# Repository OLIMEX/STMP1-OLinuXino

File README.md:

# STMP1-OLinuXino

STMP1 (es-ti-em-pai) OLinuXino (o-linux-ino) is based on STM32MP1XX Dual Core Cortex-A7 + Cortex-M4 microprocessors from ST Microelectronics. The Cortex-A7 can run Linux/Android OS while Cortex-M4 handle Real-Time events.

Features are:

- mainline Linux support
- automotive -40+125C operating temperature on all devices!
- 1GB DDR3L
- Gigabit Ethernet interface
- Three USB 2.0
- Two FD-CAN
- Two ADC
- Two DAC
- Camera IF
- Six I2C
- Three I2S
- Three SD MMC
- FMC (NAND) Flash
- Six SPI
- Four UART
- MIPI DSI 3Gb (157 only)
- Secure Boot
- Crypto Hash (C version only)

STMP1-OLinuXino is designed in the same size and connector locations as A20-OLinuXino-LIME2 so being replacable and pin to pin compatible. 

STMP1-OLinuXino is manufactured in -40+125C operating temperature and targets industrial applications.

# License
- Hardware is with CERN OHL v1.2 license
- Software is with GPLv3 license
- Documentation is with CC BY-SA 4.0 license

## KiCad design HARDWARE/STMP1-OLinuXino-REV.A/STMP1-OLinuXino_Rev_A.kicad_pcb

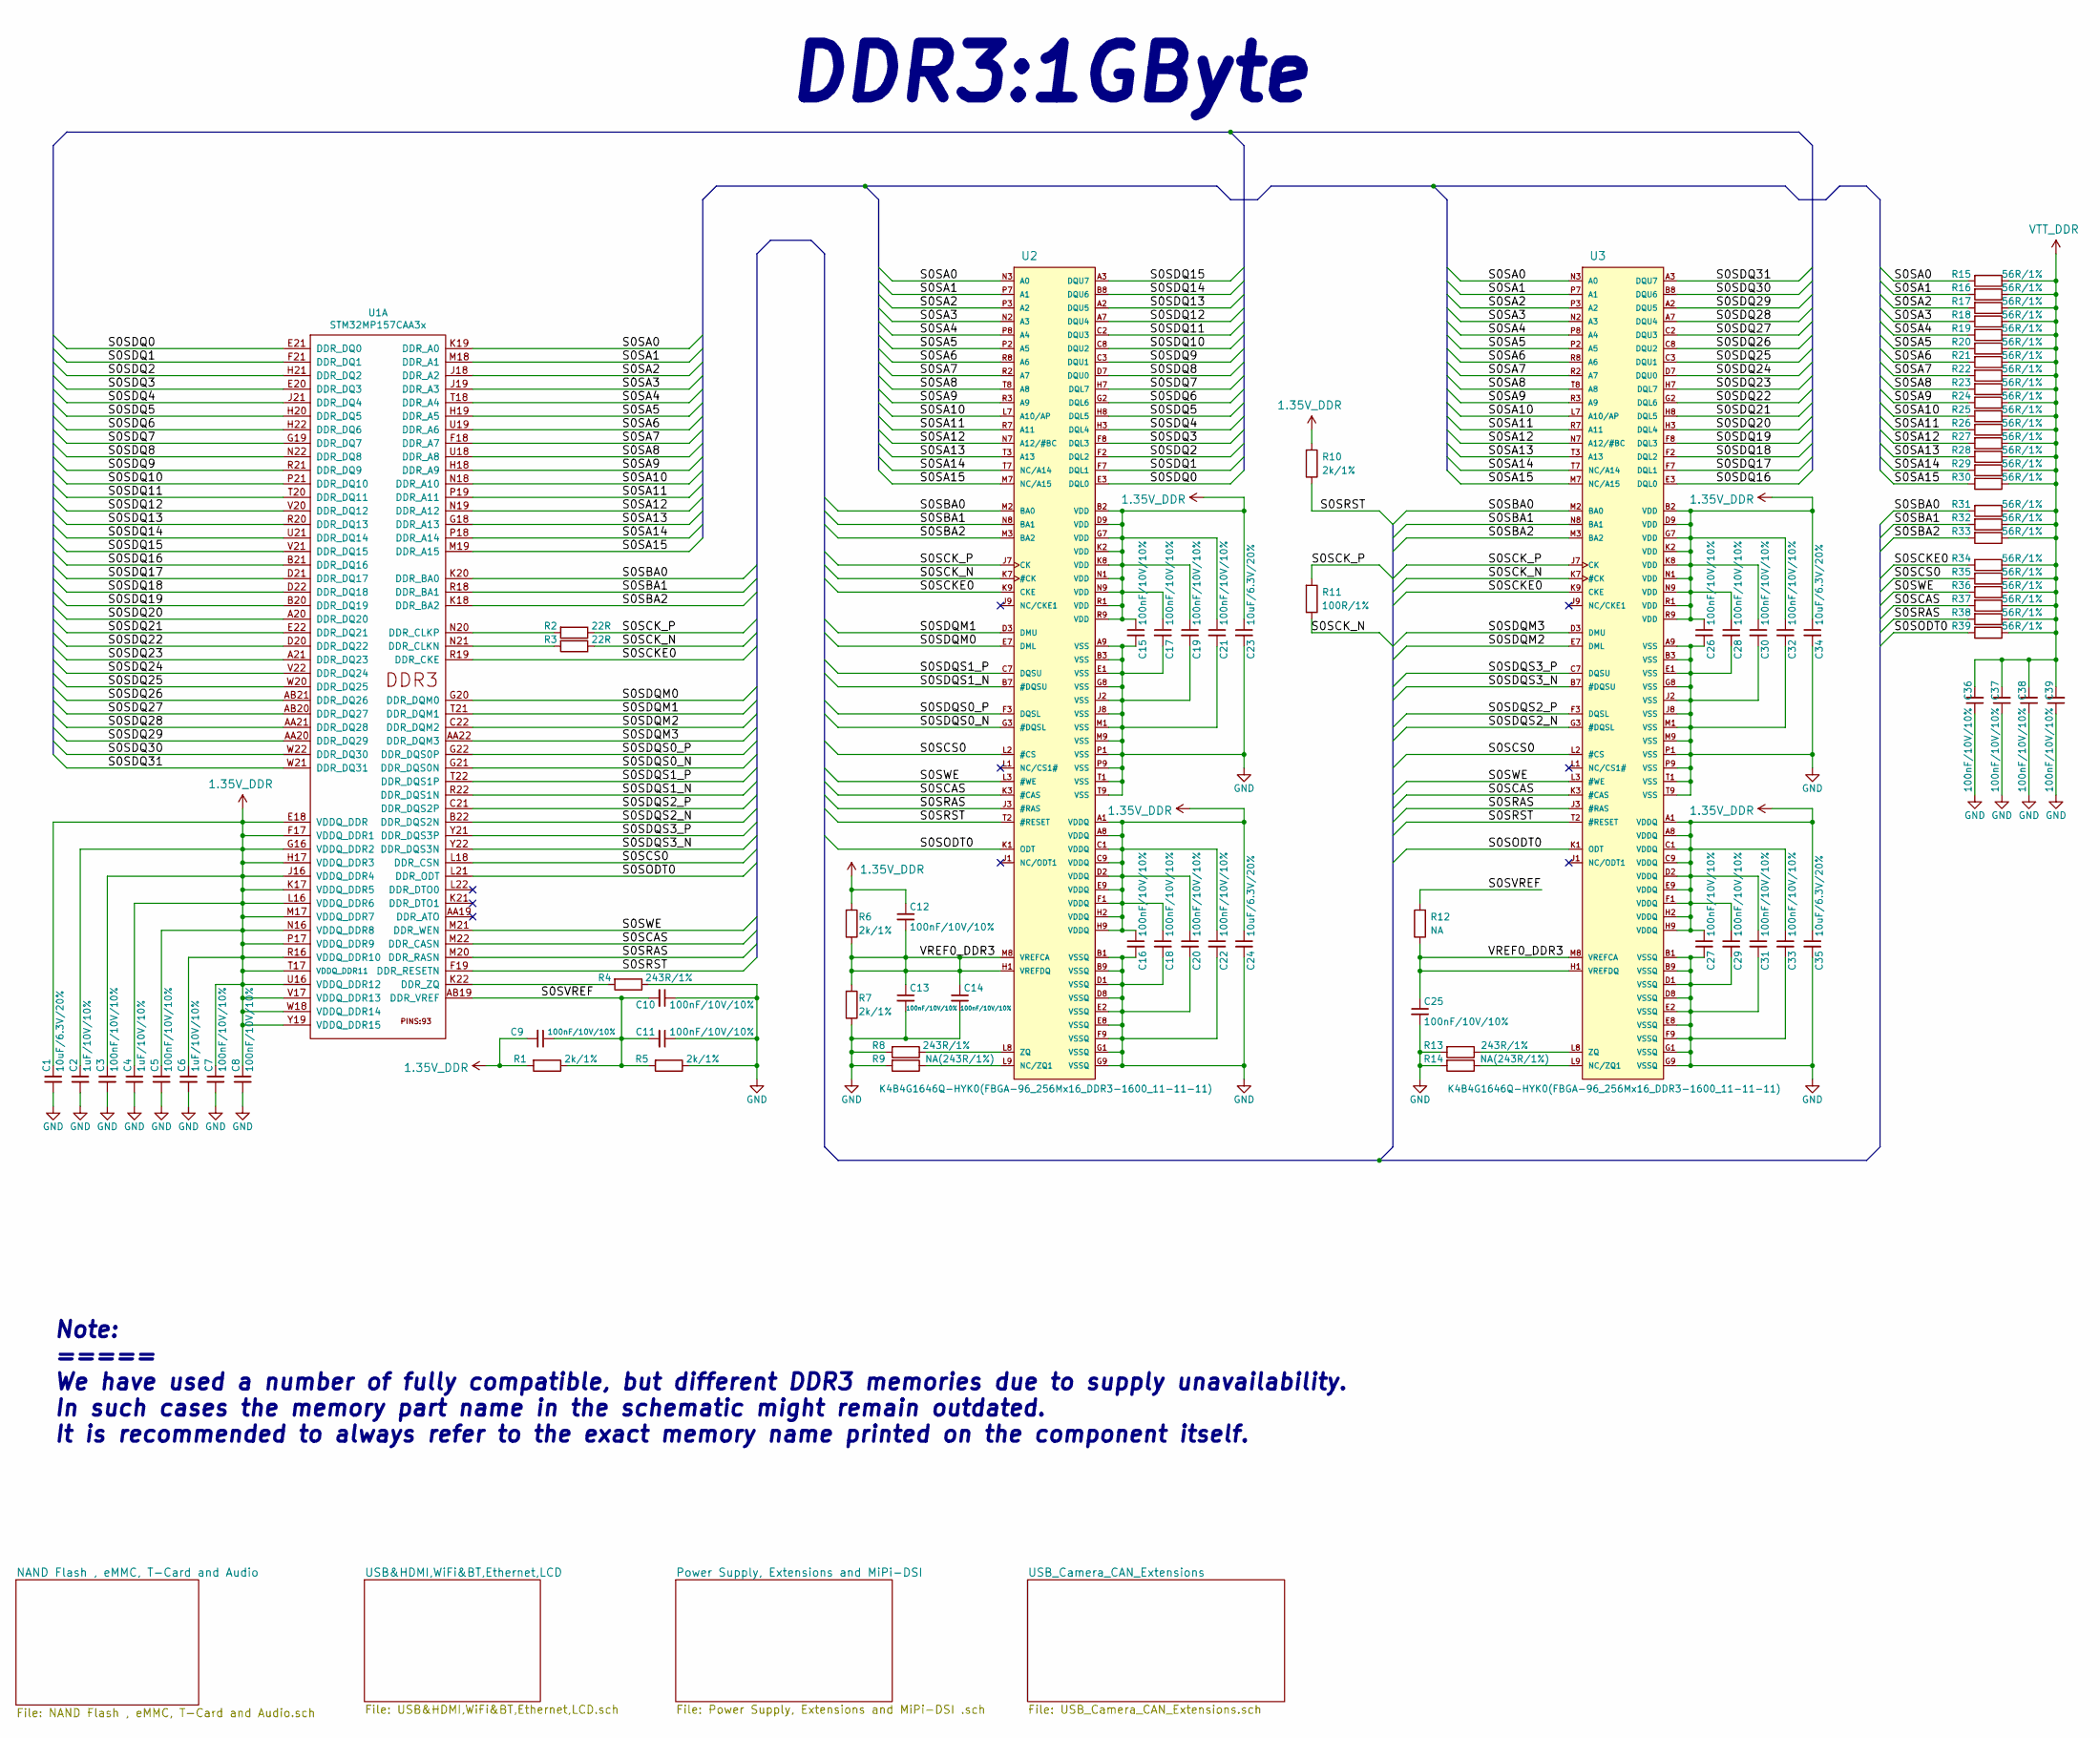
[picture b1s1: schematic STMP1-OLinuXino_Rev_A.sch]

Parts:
C1, C23, C24, C34, C35: 10uF/6.3V/20%; C_0603_5MIL_DWS
C2, C4, C6: 1uF/10V/10%; C_0603_5MIL_DWS
C3, C5, C7, C8, C9, C10, C11, C12, C13, C14, C15, C16, C17, C18, C19, C20, C21, C22, C25, C26, C27, C28, C29, C30, C31, C32, C33, C36, C37, C38, C39: 100nF/10V/10%; C_0402_5MIL_DWS
R1, R5, R6, R7, R10: 2k/1%; R_0402_5MIL_DWS
R2, R3: 22R; R_0402_5MIL_DWS
R4, R8, R13: 243R/1%; R_0402_5MIL_DWS
R9, R14: NA(243R/1%); R_0402_5MIL_DWS
R11: 100R/1%; R_0402_5MIL_DWS
R12: NA; R_0402_5MIL_DWS
R15, R16, R17, R18, R19, R20, R21, R22, R23, R24, R25, R26, R27, R28, R29, R30, R31, R32, R33, R34, R35, R36, R37, R38, R39: 56R/1%; R_0402_5MIL_DWS
U1: STM32MP157CAA3x; LFBGA-448(Pitch-0.8mm_Pad-0.4mm_18x18x1.27mm)
U2, U3: K4B4G1646Q-HYK0(FBGA-96_256Mx16_DDR3-1600_11-11-1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; FBGA96(HYNIX_SAMSUNG_512MX16_DDR3)

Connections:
1.35V_DDR: C1.1, C2.1, C3.1, C4.1, C5.1, C6.1, C7.1, C8.1, C9.2, C12.1, C15.1, C16.1, C17.1, C18.1, C19.1, C20.1, C21.1, C22.1, C23.1, C24.1, C26.1, C27.1, C28.1, C29.1, C30.1, C31.1, C32.1, C33.1, C34.1, C35.1, R1.2, R6.2, R10.2, U1.E18 (VDDQ_DDR), U1.F17 (VDDQ_DDR1), U1.G16 (VDDQ_DDR2), U1.H17 (VDDQ_DDR3), U1.J16 (VDDQ_DDR4), U1.K17 (VDDQ_DDR5), U1.L16 (VDDQ_DDR6), U1.M17 (VDDQ_DDR7), U1.N16 (VDDQ_DDR8), U1.P17 (VDDQ_DDR9), U1.R16 (VDDQ_DDR10), U1.T17 (VDDQ_DDR11), U1.U16 (VDDQ_DDR12), U1.V17 (VDDQ_DDR13), U1.W18 (VDDQ_DDR14), U1.Y19 (VDDQ_DDR15), U2.A1 (VDDQ), U2.A8 (VDDQ), U2.B2 (VDD), U2.C1 (VDDQ), U2.C9 (VDDQ), U2.D2 (VDDQ), U2.D9 (VDD), U2.E9 (VDDQ), U2.F1 (VDDQ), U2.G7 (VDD), U2.H2 (VDDQ), U2.H9 (VDDQ), U2.K2 (VDD), U2.K8 (VDD), U2.N1 (VDD), U2.N9 (VDD), U2.R1 (VDD), U2.R9 (VDD), U3.A1 (VDDQ), U3.A8 (VDDQ), U3.B2 (VDD), U3.C1 (VDDQ), U3.C9 (VDDQ), U3.D2 (VDDQ), U3.D9 (VDD), U3.E9 (VDDQ), U3.F1 (VDDQ), U3.G7 (VDD), U3.H2 (VDDQ), U3.H9 (VDDQ), U3.K2 (VDD), U3.K8 (VDD), U3.N1 (VDD), U3.N9 (VDD), U3.R1 (VDD), U3.R9 (VDD); also elsewhere on the board
/S0SA0: R15.2, U1.K19 (DDR_A0), U2.N3 (A0), U3.N3 (A0)
/S0SA1: R16.2, U1.M18 (DDR_A1), U2.P7 (A1), U3.P7 (A1)
/S0SA2: R17.2, U1.J18 (DDR_A2), U2.P3 (A2), U3.P3 (A2)
/S0SA3: R18.2, U1.J19 (DDR_A3), U2.N2 (A3), U3.N2 (A3)
/S0SA4: R19.2, U1.T18 (DDR_A4), U2.P8 (A4), U3.P8 (A4)
/S0SA5: R20.2, U1.H19 (DDR_A5), U2.P2 (A5), U3.P2 (A5)
/S0SA6: R21.2, U1.U19 (DDR_A6), U2.R8 (A6), U3.R8 (A6)
/S0SA7: R22.2, U1.F18 (DDR_A7), U2.R2 (A7), U3.R2 (A7)
/S0SA8: R23.2, U1.U18 (DDR_A8), U2.T8 (A8), U3.T8 (A8)
/S0SA9: R24.2, U1.H18 (DDR_A9), U2.R3 (A9), U3.R3 (A9)
/S0SA10: R25.2, U1.N18 (DDR_A10), U2.L7 (A10/AP), U3.L7 (A10/AP)
/S0SA11: R26.2, U1.P19 (DDR_A11), U2.R7 (A11), U3.R7 (A11)
/S0SA12: R27.2, U1.N19 (DDR_A12), U2.N7 (A12/#BC), U3.N7 (A12/#BC)
/S0SA13: R28.2, U1.G18 (DDR_A13), U2.T3 (A13), U3.T3 (A13)
/S0SA14: R29.2, U1.P18 (DDR_A14), U2.T7 (NC/A14), U3.T7 (NC/A14)
/S0SA15: R30.2, U1.M19 (DDR_A15), U2.M7 (NC/A15), U3.M7 (NC/A15)
/S0SBA0: R31.2, U1.K20 (DDR_BA0), U2.M2 (BA0), U3.M2 (BA0)
/S0SBA1: R32.2, U1.R18 (DDR_BA1), U2.N8 (BA1), U3.N8 (BA1)
/S0SBA2: R33.2, U1.K18 (DDR_BA2), U2.M3 (BA2), U3.M3 (BA2)
/S0SCAS: R37.2, U1.M22 (DDR_CASN), U2.K3 (#CAS), U3.K3 (#CAS)
/S0SCKE0: R34.2, U1.R19 (DDR_CKE), U2.K9 (CKE), U3.K9 (CKE)
/S0SCK_N: R3.1, R11.1, U2.K7 (#CK), U3.K7 (#CK)
/S0SCK_P: R2.1, R11.2, U2.J7 (CK), U3.J7 (CK)
/S0SCS0: R35.2, U1.L18 (DDR_CSN), U2.L2 (#CS), U3.L2 (#CS)
/S0SDQ0: U1.E21 (DDR_DQ0), U2.E3 (DQL0)
/S0SDQ1: U1.F21 (DDR_DQ1), U2.F7 (DQL1)
/S0SDQ2: U1.H21 (DDR_DQ2), U2.F2 (DQL2)
/S0SDQ3: U1.E20 (DDR_DQ3), U2.F8 (DQL3)
/S0SDQ4: U1.J21 (DDR_DQ4), U2.H3 (DQL4)
/S0SDQ5: U1.H20 (DDR_DQ5), U2.H8 (DQL5)
/S0SDQ6: U1.H22 (DDR_DQ6), U2.G2 (DQL6)
/S0SDQ7: U1.G19 (DDR_DQ7), U2.H7 (DQL7)
/S0SDQ8: U1.N22 (DDR_DQ8), U2.D7 (DQU0)
/S0SDQ9: U1.R21 (DDR_DQ9), U2.C3 (DQU1)
/S0SDQ10: U1.P21 (DDR_DQ10), U2.C8 (DQU2)
/S0SDQ11: U1.T20 (DDR_DQ11), U2.C2 (DQU3)
/S0SDQ12: U1.V20 (DDR_DQ12), U2.A7 (DQU4)
/S0SDQ13: U1.R20 (DDR_DQ13), U2.A2 (DQU5)
/S0SDQ14: U1.U21 (DDR_DQ14), U2.B8 (DQU6)
/S0SDQ15: U1.V21 (DDR_DQ15), U2.A3 (DQU7)
/S0SDQ16: U1.B21 (DDR_DQ16), U3.E3 (DQL0)
/S0SDQ17: U1.D21 (DDR_DQ17), U3.F7 (DQL1)
/S0SDQ18: U1.D22 (DDR_DQ18), U3.F2 (DQL2)
/S0SDQ19: U1.B20 (DDR_DQ19), U3.F8 (DQL3)
/S0SDQ20: U1.A20 (DDR_DQ20), U3.H3 (DQL4)
/S0SDQ21: U1.E22 (DDR_DQ21), U3.H8 (DQL5)
/S0SDQ22: U1.D20 (DDR_DQ22), U3.G2 (DQL6)
/S0SDQ23: U1.A21 (DDR_DQ23), U3.H7 (DQL7)
/S0SDQ24: U1.V22 (DDR_DQ24), U3.D7 (DQU0)
/S0SDQ25: U1.W20 (DDR_DQ25), U3.C3 (DQU1)
/S0SDQ26: U1.AB21 (DDR_DQ26), U3.C8 (DQU2)
/S0SDQ27: U1.AB20 (DDR_DQ27), U3.C2 (DQU3)
/S0SDQ28: U1.AA21 (DDR_DQ28), U3.A7 (DQU4)
/S0SDQ29: U1.AA20 (DDR_DQ29), U3.A2 (DQU5)
/S0SDQ30: U1.W22 (DDR_DQ30), U3.B8 (DQU6)
/S0SDQ31: U1.W21 (DDR_DQ31), U3.A3 (DQU7)
/S0SDQM0: U1.G20 (DDR_DQM0), U2.E7 (DML)
/S0SDQM1: U1.T21 (DDR_DQM1), U2.D3 (DMU)
/S0SDQM2: U1.C22 (DDR_DQM2), U3.E7 (DML)
/S0SDQM3: U1.AA22 (DDR_DQM3), U3.D3 (DMU)
/S0SDQS0_N: U1.G21 (DDR_DQS0N), U2.G3 (#DQSL)
/S0SDQS0_P: U1.G22 (DDR_DQS0P), U2.F3 (DQSL)
/S0SDQS1_N: U1.R22 (DDR_DQS1N), U2.B7 (#DQSU)
/S0SDQS1_P: U1.T22 (DDR_DQS1P), U2.C7 (DQSU)
/S0SDQS2_N: U1.B22 (DDR_DQS2N), U3.G3 (#DQSL)
/S0SDQS2_P: U1.C21 (DDR_DQS2P), U3.F3 (DQSL)
/S0SDQS3_N: U1.Y22 (DDR_DQS3N), U3.B7 (#DQSU)
/S0SDQS3_P: U1.Y21 (DDR_DQS3P), U3.C7 (DQSU)
/S0SODT0: R39.2, U1.L21 (DDR_ODT), U2.K1 (ODT), U3.K1 (ODT)
/S0SRAS: R38.2, U1.M20 (DDR_RASN), U2.J3 (#RAS), U3.J3 (#RAS)
/S0SRST: R10.1, U1.F19 (DDR_RESETN), U2.T2 (#RESET), U3.T2 (#RESET)
/S0SVREF: C9.1, C10.2, C11.2, R1.1, R5.2, R12.2, U1.AB19 (DDR_VREF)
/S0SWE: R36.2, U1.M21 (DDR_WEN), U2.L3 (#WE), U3.L3 (#WE)
/VREF0_DDR3: C12.2, C13.1, C14.1, C25.1, R6.1, R7.2, R12.1, U2.H1 (VREFDQ), U2.M8 (VREFCA), U3.H1 (VREFDQ), U3.M8 (VREFCA)
GND: C1.2, C2.2, C3.2, C4.2, C5.2, C6.2, C7.2, C8.2, C10.1, C11.1, C13.2, C14.2, C15.2, C16.2, C17.2, C18.2, C19.2, C20.2, C21.2, C22.2, C23.2, C24.2, C25.2, C26.2, C27.2, C28.2, C29.2, C30.2, C31.2, C32.2, C33.2, C34.2, C35.2, C36.1, C37.1, C38.1, C39.1, R4.1, R5.1, R7.1, R8.2, R9.2, R13.2, R14.2, U2.A9 (VSS), U2.B1 (VSSQ), U2.B3 (VSS), U2.B9 (VSSQ), U2.D1 (VSSQ), U2.D8 (VSSQ), U2.E1 (VSS), U2.E2 (VSSQ), U2.E8 (VSSQ), U2.F9 (VSSQ), U2.G1 (VSSQ), U2.G8 (VSS), U2.G9 (VSSQ), U2.J2 (VSS), U2.J8 (VSS), U2.M1 (VSS), U2.M9 (VSS), U2.P1 (VSS), U2.P9 (VSS), U2.T1 (VSS), U2.T9 (VSS), U3.A9 (VSS), U3.B1 (VSSQ), U3.B3 (VSS), U3.B9 (VSSQ), U3.D1 (VSSQ), U3.D8 (VSSQ), U3.E1 (VSS), U3.E2 (VSSQ), U3.E8 (VSSQ), U3.F9 (VSSQ), U3.G1 (VSSQ), U3.G8 (VSS), U3.G9 (VSSQ), U3.J2 (VSS), U3.J8 (VSS), U3.M1 (VSS), U3.M9 (VSS), U3.P1 (VSS), U3.P9 (VSS), U3.T1 (VSS), U3.T9 (VSS); also elsewhere on the board
unnamed: R2.2, U1.N20 (DDR_CLKP)
unnamed: R3.2, U1.N21 (DDR_CLKN)
unnamed: R4.2, U1.K22 (DDR_ZQ)
unnamed: R8.1, U2.L8 (ZQ)
unnamed: R9.1, U2.L9 (NC/ZQ1)
unnamed: R13.1, U3.L8 (ZQ)
unnamed: R14.1, U3.L9 (NC/ZQ1)
VTT_DDR: C36.2, C37.2, C38.2, C39.2, R15.1, R16.1, R17.1, R18.1, R19.1, R20.1, R21.1, R22.1, R23.1, R24.1, R25.1, R26.1, R27.1, R28.1, R29.1, R30.1, R31.1, R32.1, R33.1, R34.1, R35.1, R36.1, R37.1, R38.1, R39.1; also elsewhere on the board

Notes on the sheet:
DDR3:1GByte
Note: ===== We have used a number of fully compatible, but different DDR3 memories due to supply unavailability. In such cases the memory part name in the schematic might remain outdated. It is recommended to always refer to the exact memory name printed on the component itself.

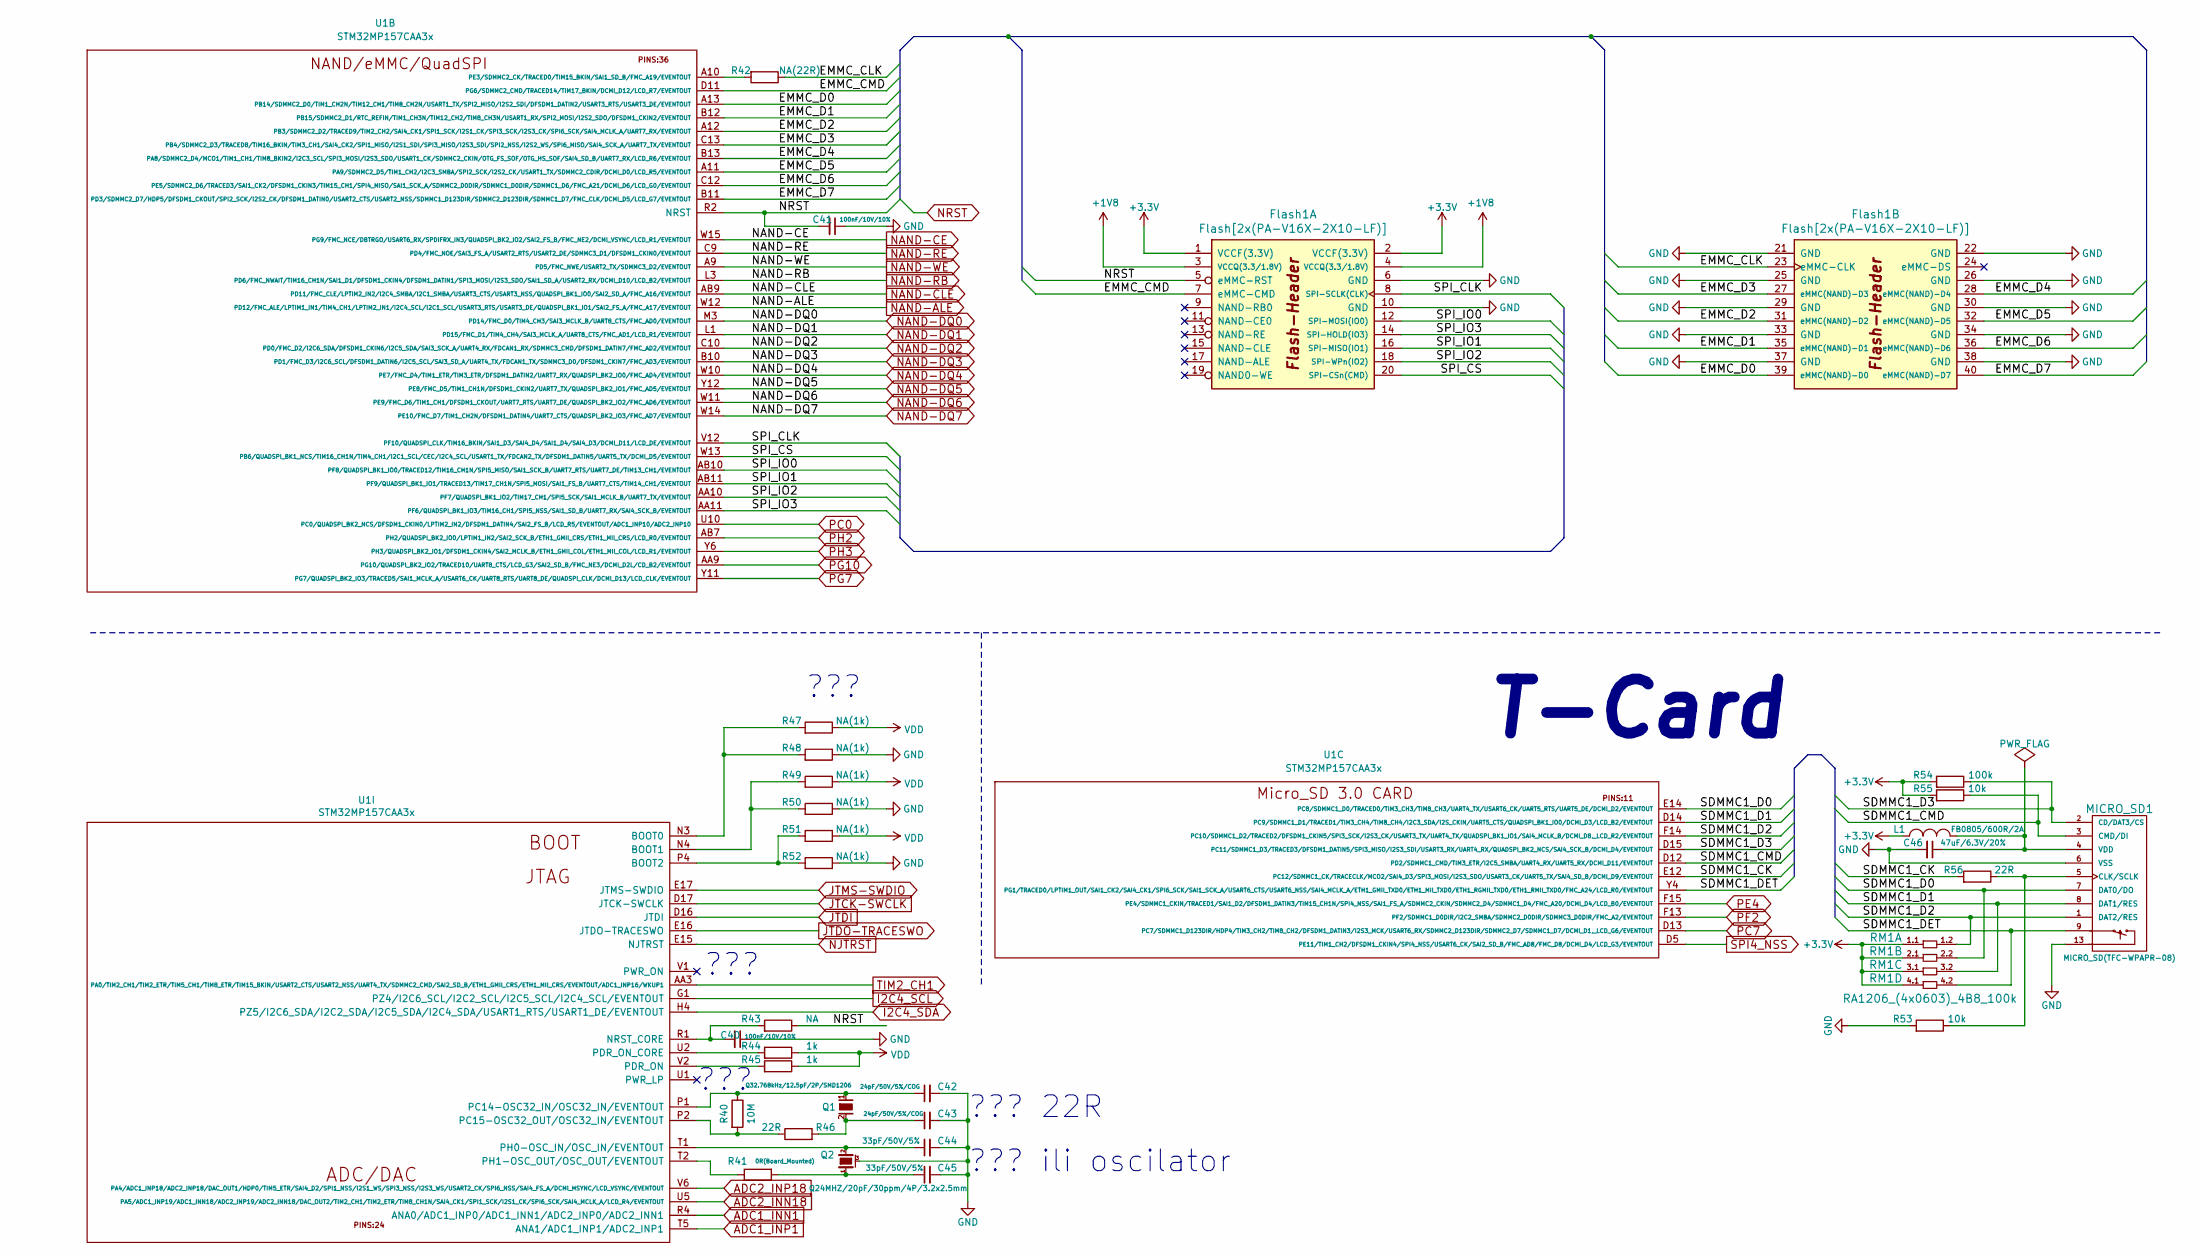
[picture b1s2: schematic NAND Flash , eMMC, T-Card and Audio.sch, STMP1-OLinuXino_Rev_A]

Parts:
C40, C41: 100nF/10V/10%; C_0402_5MIL_DWS
C42, C43: 24pF/50V/5%/COG; C_0402_5MIL_DWS
C44, C45: 33pF/50V/5%; C_0402_5MIL_DWS
C46: 47uF/6.3V/20%; C_0805_5MIL_DWS
Flash1: Flash[2x(PA-V16X-2X10-LF)]
L1: FB0805/600R/2A; L_0805_5MIL_DWS
MICRO_SD1: MICRO_SD(TFC-WPAPR-08); TFC-WPAPR-08
Q1: Q32.768kHz/12.5pF/2P/SMD1206; CM7V-T1A(Crystal_Package-1206_3.20x1.50x0.65mm)
Q2: Q24MHZ/20pF/30ppm/4P/3.2x2.5mm; TSX-3.2x2.5mm_GND(3)
R40: 10M; R_0402_5MIL_DWS
R41: 0R(Board_Mounted); R_0402_5MIL_0R(Board_Mounted)
R42: NA(22R); R_0402_5MIL_DWS
R43: NA; R_0402_5MIL_DWS
R44, R45: 1k; R_0402_5MIL_DWS
R46, R56: 22R; R_0402_5MIL_DWS
R47, R48, R49, R50, R51, R52: NA(1k); R_0402_5MIL_DWS
R53, R55: 10k; R_0402_5MIL_DWS
R54: 100k; R_0402_5MIL_DWS
RM1: RA1206_(4x0603)_4B8_100k; RA1206_(4X0603)_4B8_xx
U1: STM32MP157CAA3x; LFBGA-448(Pitch-0.8mm_Pad-0.4mm_18x18x1.27mm)

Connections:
+3V3: Flash1.1 (VCCF(3.3V)), Flash1.2 (VCCF(3.3V)), L1.1, R54.2, R55.2, RM1.1.1, RM1.2.1, RM1.3.1, RM1.4.1; also elsewhere on the board
/NAND Flash , eMMC, T-Card and Audio/EMMC_CLK: Flash1.23 (eMMC-CLK), R42.1
/NAND Flash , eMMC, T-Card and Audio/EMMC_CMD: Flash1.7 (eMMC-CMD), U1.D11 (PG6/SDMMC2_CMD/TRACED14/TIM17_BKIN/DCMI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)
/NAND Flash , eMMC, T-Card and Audio/EMMC_D0: Flash1.39 (eMMC(NAND)-D0), U1.A13 (PB14/SDMMC2_D0/TIM1_CH2N/TIM12_CH1/TIM8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)
/NAND Flash , eMMC, T-Card and Audio/EMMC_D1: Flash1.35 (eMMC(NAND)-D1), U1.B12 (PB15/SDMMC2_D1/RTC_REFIN/TIM1_CH3N/TIM1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)
/NAND Flash , eMMC, T-Card and Audio/EMMC_D2: Flash1.31 (eMMC(NAND)-D2), U1.A12 (PB3/SDMMC2_D2/TRACED9/TIM2_CH2/SAI4_CK1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)
/NAND Flash , eMMC, T-Card and Audio/EMMC_D3: Flash1.27 (eMMC(NAND)-D3), U1.C13 (PB4/SDMMC2_D3/TRACED8/TIM16_BKIN/TIM3_C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)
/NAND Flash , eMMC, T-Card and Audio/EMMC_D4: Flash1.28 (eMMC(NAND)-D4), U1.B13 (PA8/SDMMC2_D4/MCO1/TIM1_CH1/TIM8_BKIN2/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)
/NAND Flash , eMMC, T-Card and Audio/EMMC_D5: Flash1.32 (eMMC(NAND)-D5), U1.A11 (PA9/SDMMC2_D5/TIM1_CH2/I2C3_SMBA/SPI2_S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)
/NAND Flash , eMMC, T-Card and Audio/EMMC_D6: Flash1.36 (eMMC(NAND)-D6), U1.C12 (PE5/SDMMC2_D6/TRACED3/SAI1_CK2/DFSDM1_C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)
/NAND Flash , eMMC, T-Card and Audio/EMMC_D7: Flash1.40 (eMMC(NAND)-D7), U1.B11 (PD3/SDMMC2_D7/HDP5/DFSDM1_CKOUT/SPI2_SC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)
/NAND Flash , eMMC, T-Card and Audio/SDMMC1_CK: R56.2, U1.E12 (PC12/SDMMC1_CK/TRACECLK/MCO2/SAI4_D3/SP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)
/NAND Flash , eMMC, T-Card and Audio/SDMMC1_CMD: MICRO_SD1.3 (CMD/DI), R55.1, U1.D12 (PD2/SDMMC1_CMD/TIM3_ETR/I2C5_SMBA/UART4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)
/NAND Flash , eMMC, T-Card and Audio/SDMMC1_D0: MICRO_SD1.7 (DAT0/DO), RM1.2.2, U1.E14 (PC8/SDMMC1_D0/TRACED0/TIM3_CH3/TIM8_CH3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)
/NAND Flash , eMMC, T-Card and Audio/SDMMC1_D1: MICRO_SD1.8 (DAT1/RES), RM1.3.2, U1.D14 (PC9/SDMMC1_D1/TRACED1/TIM3_CH4/TIM8_CH4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)
/NAND Flash , eMMC, T-Card and Audio/SDMMC1_D2: MICRO_SD1.1 (DAT2/RES), RM1.1.2, U1.F14 (PC10/SDMMC1_D2/TRACED2/DFSDM1_CKIN5/SPI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)
/NAND Flash , eMMC, T-Card and Audio/SDMMC1_D3: MICRO_SD1.2 (CD/DAT3/CS), R54.1, U1.D15 (PC11/SDMMC1_D3/TRACED3/DFSDM1_DATIN5/SP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)
/NAND Flash , eMMC, T-Card and Audio/SDMMC1_DET: MICRO_SD1.9, RM1.4.2, U1.Y4 (PG1/TRACED0/LPTIM1_OUT/SAI1_CK2/SAI4_CK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)
/NAND Flash , eMMC, T-Card and Audio/SPI_CLK: Flash1.8 (SPI-SCLK(CLK)), U1.V12 (PF10/QUADSPI_CLK/TIM16_BKIN/SAI1_D3/SAI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)
/NAND Flash , eMMC, T-Card and Audio/SPI_CS: Flash1.20 (SPI-CSn(CMD)), U1.W13 (PB6/QUADSPI_BK1_NCS/TIM16_CH1N/TIM4_CH1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)
/NAND Flash , eMMC, T-Card and Audio/SPI_IO0: Flash1.12 (SPI-MOSI(IO0)), U1.AB10 (PF8/QUADSPI_BK1_IO0/TRACED12/TIM16_CH1N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)
/NAND Flash , eMMC, T-Card and Audio/SPI_IO1: Flash1.16 (SPI-MISO(IO1)), U1.AB11 (PF9/QUADSPI_BK1_IO1/TRACED13/TIM17_CH1N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)
/NAND Flash , eMMC, T-Card and Audio/SPI_IO2: Flash1.18 (SPI-WPn(IO2)), U1.AA10 (PF7/QUADSPI_BK1_IO2/TIM17_CH1/SPI5_SCK/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)
/NAND Flash , eMMC, T-Card and Audio/SPI_IO3: Flash1.14 (SPI-HOLD(IO3)), U1.AA11 (PF6/QUADSPI_BK1_IO3/TIM16_CH1/SPI5_NSS/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)
ADC1_INN1: U1.R4 (ANA0/ADC1_INP0/ADC1_INN1/ADC2_INP0/ADC2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); also elsewhere on the board
ADC1_INP1: U1.T5 (ANA1/ADC1_INP1/ADC2_INP1); also elsewhere on the board
ADC2_INN18: U1.U5 (PA5/ADC1_INP19/ADC1_INN18/ADC2_INP19/AD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); also elsewhere on the board
ADC2_INP18: U1.V6 (PA4/ADC1_INP18/ADC2_INP18/DAC_OUT1/HDP0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); also elsewhere on the board
GND: C40.1, C41.1, C42.2, C43.2, C44.2, C45.2, C46.2, Flash1.6 (GND), Flash1.10 (GND), Flash1.21 (GND), Flash1.22 (GND), Flash1.25 (GND), Flash1.26 (GND), Flash1.29 (GND), Flash1.30 (GND), Flash1.33 (GND), Flash1.34 (GND), Flash1.37 (GND), Flash1.38 (GND), MICRO_SD1.6 (VSS), MICRO_SD1.10, MICRO_SD1.11, MICRO_SD1.12, MICRO_SD1.13, Q2.3 (case), R48.1, R50.1, R52.1, R53.2; also elsewhere on the board
I2C4_SCL: U1.G1 (PZ4/I2C6_SCL/I2C2_SCL/I2C5_SCL/I2C4_SCL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); also elsewhere on the board
I2C4_SDA: U1.H4 (PZ5/I2C6_SDA/I2C2_SDA/I2C5_SDA/I2C4_SDA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); also elsewhere on the board
JTCK-SWCLK: U1.D17 (JTCK-SWCLK); also elsewhere on the board
JTDI: U1.D16 (JTDI); also elsewhere on the board
JTDO-TRACESWO: U1.E16 (JTDO-TRACESWO); also elsewhere on the board
JTMS-SWDIO: U1.E17 (JTMS-SWDIO); also elsewhere on the board
NAND-ALE: U1.W12 (PD12/FMC_ALE/LPTIM1_IN1/TIM4_CH1/LPTIM2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); also elsewhere on the board
NAND-CE: U1.W15 (PG9/FMC_NCE/DBTRGO/USART6_RX/SPDIFRX_IN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); also elsewhere on the board
NAND-CLE: U1.AB9 (PD11/FMC_CLE/LPTIM2_IN2/I2C4_SMBA/I2C1_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); also elsewhere on the board
NAND-DQ0: U1.M3 (PD14/FMC_D0/TIM4_CH3/SAI3_MCLK_B/UART8_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); also elsewhere on the board
NAND-DQ1: U1.L1 (PD15/FMC_D1/TIM4_CH4/SAI3_MCLK_A/UART8_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); also elsewhere on the board
NAND-DQ2: U1.C10 (PD0/FMC_D2/I2C6_SDA/DFSDM1_CKIN6/I2C5_S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); also elsewhere on the board
NAND-DQ3: U1.B10 (PD1/FMC_D3/I2C6_SCL/DFSDM1_DATIN6/I2C5_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); also elsewhere on the board
NAND-DQ4: U1.W10 (PE7/FMC_D4/TIM1_ETR/TIM3_ETR/DFSDM1_DAT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); also elsewhere on the board
NAND-DQ5: U1.Y12 (PE8/FMC_D5/TIM1_CH1N/DFSDM1_CKIN2/UART7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); also elsewhere on the board
NAND-DQ6: U1.W11 (PE9/FMC_D6/TIM1_CH1/DFSDM1_CKOUT/UART7_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); also elsewhere on the board
NAND-DQ7: U1.W14 (PE10/FMC_D7/TIM1_CH2N/DFSDM1_DATIN4/UAR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); also elsewhere on the board
NAND-RB: U1.L3 (PD6/FMC_NWAIT/TIM16_CH1N/SAI1_D1/DFSDM1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); also elsewhere on the board
NAND-RE: U1.C9 (PD4/FMC_NOE/SAI3_FS_A/USART2_RTS/USART2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); also elsewhere on the board
NAND-WE: U1.A9 (PD5/FMC_NWE/USART2_TX/SDMMC3_D2/EVENTOUT); also elsewhere on the board
NJTRST: U1.E15 (NJTRST); also elsewhere on the board
NRST: C41.2, Flash1.5 (eMMC-RST), R43.1, U1.R2 (NRST); also elsewhere on the board
unnamed: C40.2, R43.2, U1.R1 (NRST_CORE)
unnamed: C42.1, Q1.1, R40.1, U1.P1 (PC14-OSC32_IN/OSC32_IN/EVENTOUT)
unnamed: C43.1, Q1.2, R46.2
unnamed: C44.1, Q2.2, U1.T1 (PH0-OSC_IN/OSC_IN/EVENTOUT)
unnamed: C45.1, Q2.1, R41.2
unnamed: C46.1, L1.2, MICRO_SD1.4 (VDD)
unnamed: MICRO_SD1.5 (CLK/SCLK), R53.1, R56.1
unnamed: R40.2, R46.1, U1.P2 (PC15-OSC32_OUT/OSC32_IN/EVENTOUT)
unnamed: R41.1, U1.T2 (PH1-OSC_OUT/OSC_OUT/EVENTOUT)
unnamed: R42.2, U1.A10 (PE3/SDMMC2_CK/TRACED0/TIM15_BKIN/SAI1_S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)
unnamed: R44.2, U1.U2 (PDR_ON_CORE)
unnamed: R45.2, U1.V2 (PDR_ON)
unnamed: R47.2, R48.2, U1.N3 (BOOT0)
unnamed: R49.2, R50.2, U1.N4 (BOOT1)
unnamed: R51.2, R52.2, U1.P4 (BOOT2)
PC0: U1.U10 (PC0/QUADSPI_BK2_NCS/DFSDM1_CKIN0/LPTIM2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); also elsewhere on the board
PC7: U1.D13 (PC7/SDMMC1_D123DIR/HDP4/TIM3_CH2/TIM8_C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); also elsewhere on the board
PE4: U1.F15 (PE4/SDMMC1_CKIN/TRACED1/SAI1_D2/DFSDM1_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); also elsewhere on the board
PF2: U1.F13 (PF2/SDMMC1_D0DIR/I2C2_SMBA/SDMMC2_D0DIR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); also elsewhere on the board
PG7: U1.Y11 (PG7/QUADSPI_BK2_IO3/TRACED5/SAI1_MCLK_A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); also elsewhere on the board
PG10: U1.AA9 (PG10/QUADSPI_BK2_IO2/TRACED10/UART8_CTS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); also elsewhere on the board
PH2: U1.AB7 (PH2/QUADSPI_BK2_IO0/LPTIM1_IN2/SAI2_SCK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); also elsewhere on the board
PH3: U1.Y6 (PH3/QUADSPI_BK2_IO1/DFSDM1_CKIN4/SAI2_M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); also elsewhere on the board
SPI4_NSS: U1.D5 (PE11/TIM1_CH2/DFSDM1_CKIN4/SPI4_NSS/USA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); also elsewhere on the board
TIM2_CH1: U1.AA3 (PA0/TIM2_CH1/TIM2_ETR/TIM5_CH1/TIM8_ETR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); also elsewhere on the board
VDD: R44.1, R45.1, R47.1, R49.1, R51.1; also elsewhere on the board

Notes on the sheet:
T-Card
??? 22R
??? ili oscilator
???
